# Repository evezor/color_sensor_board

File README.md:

# Color Sensor Board
*please note this board has been deprecated.

Color Sensor board with the VEML6040 chip for color detection with built in led for low light situations.

This also has mousebites on the sensor part of the board so it can be removed and the color sensor can be mounted closer and in a smaller form factor than the larger assembly.

source files can be found here: https://github.com/evezor/v0_color_sensor_board

This board uses the Evezor Stamp STMF405 MCU

source: https://github.com/evezor/Evezor-Stamp-STMF405

Evezor® and all associated marks, logos, and designs are registered trademarks and protected by copyright. Unauthorized use or reproduction of these trademarks and copyrighted materials is strictly prohibited.

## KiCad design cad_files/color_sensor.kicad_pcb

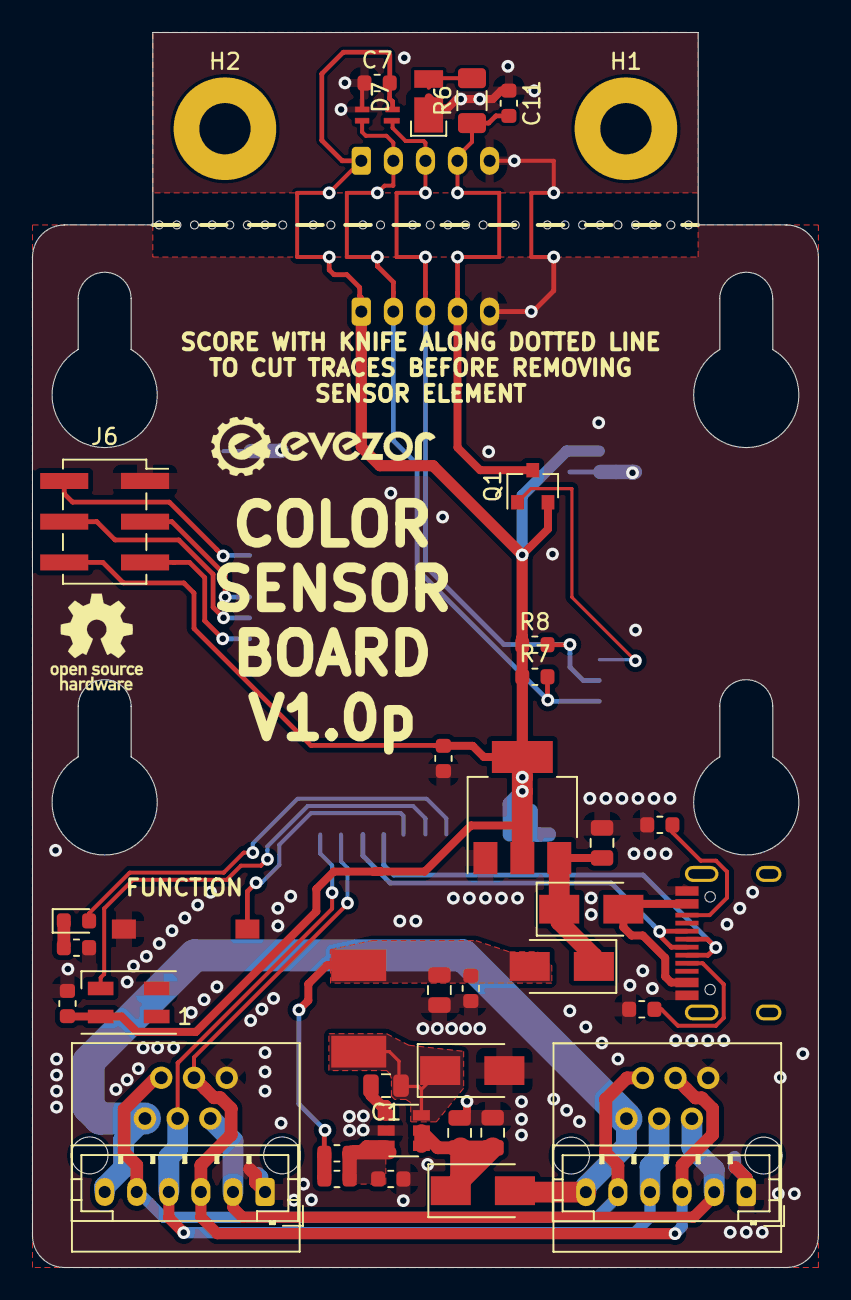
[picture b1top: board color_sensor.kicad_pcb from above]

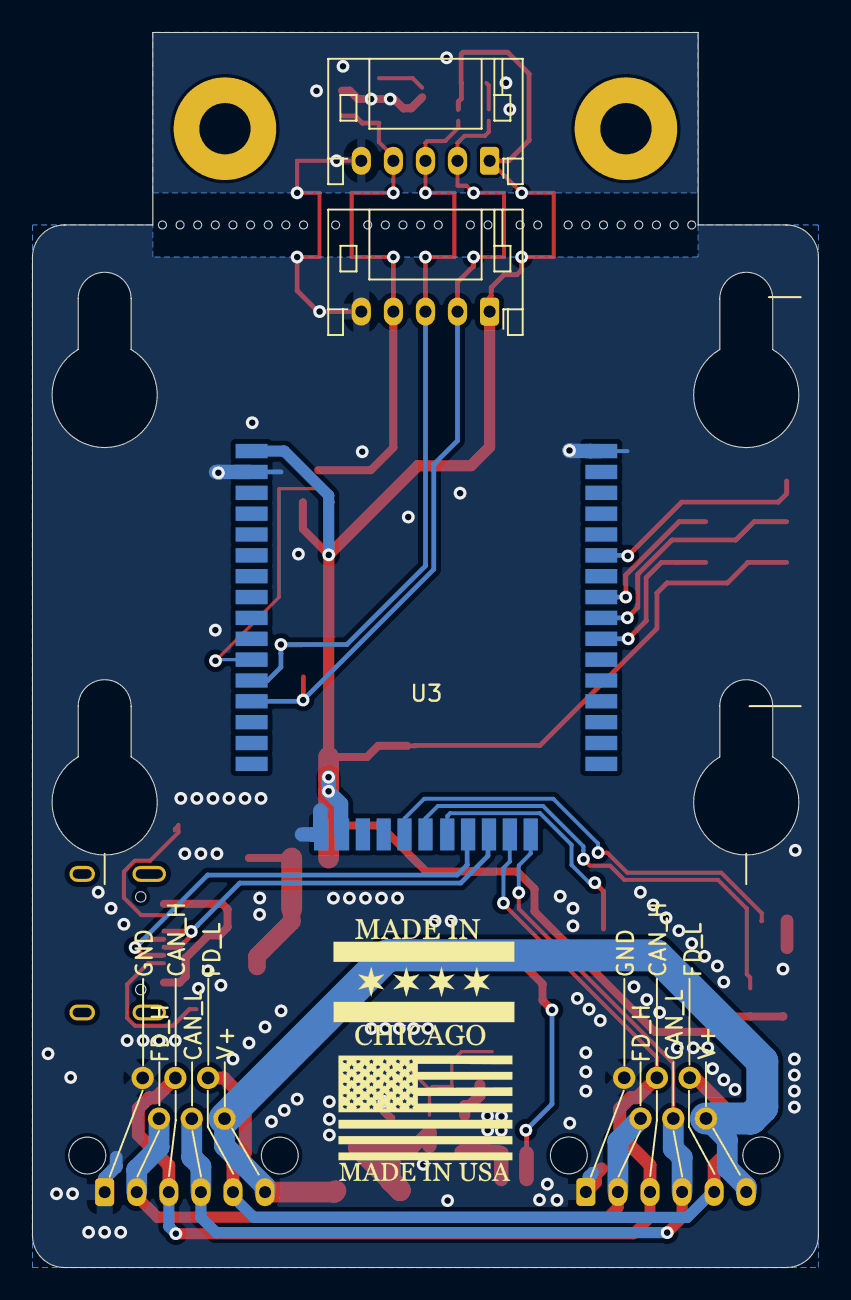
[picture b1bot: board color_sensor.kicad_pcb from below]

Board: 2 copper layers, 49.0 x 77.0 mm, 43 parts (3 on the bottom side), 31 nets.

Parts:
C1, C3: .1uF 100V; C_0805_2012Metric
C2, C5, C7, C9, C10: .1uF; C_0603_1608Metric
C4: 4.7uF; C_0805_2012Metric
C6: 22uF; C_0805_2012Metric
C8: 10uF; C_0805_2012Metric
C11: 10uF; C_0603_1608Metric
D1, D2, D4, D5: SX35_SCHOTTKY; D_SMA
D3: LED; LED_0603_1608Metric
D6: SK6812MINI; LED_SK6812MINI_PLCC4_3.5x3.5mm_P1.75mm
D7: LED; LED_WHITE_CREE_JB2835
H1, H2: MountingHole; MountingHole_3.2mm_M3_Pad
J1: USB_C_Receptacle_USB2.0; USB_C_Receptacle_HRO_TYPE-C-31-M-12
J2, J3: RJ11; RJ11_C189747_Horizontal
J4, J5: PH; JST_PH_B6B-PH-K_1x06_P2.00mm_Vertical
J6: Conn_02x03_Odd_Even; PinSocket_2x03_P2.54mm_Vertical_SMD
J7, J8: Conn_01x05; JST_PH_S5B-PH-K_1x05_P2.00mm_Horizontal
L1: 22uH; INDUCTOR_7.5X6.6_GCDA0630-220MC
Q1: FDC304P; SOT-23
R1: 10k; R_0603_1608Metric
R2: 82k; R_0603_1608Metric
R3, R4: 5.1k; R_0603_1608Metric
R5: 15k; R_0603_1608Metric
R6: 60; R_1206_3216Metric
R7, R8: 4.7k; R_0603_1608Metric
SW1: SW_Push; SWITCH_2x3_SMD_TACTILE_GREEN
U1: SY8401ABC; SOT-23-6
U2: AMS1117-3.3; SOT-223-3_TabPin2
U3: EDGE_STM32F405_CPU_V1; EDGE_STAMP
U4: SENSOR_COLOR_VEML6040

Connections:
+3V3: C7.2, C9.2, C10.1, D6.4, J6.6, J7.1, J8.1, Q1.2, R7.1, R8.1, U2.2, U3.1, U3.18, U4.4
/BACK_LIGHT: Q1.1, U3.11
/BOOT: J6.3, U3.36
/CAN_H: J2.3, J3.3, J4.3, J5.3, U3.26
/CAN_L: J2.4, J3.4, J4.4, J5.4, U3.27
/CC1: J1.A5, R4.1
/CC2: J1.B5, R3.1
/D+: J1.A6, J1.B6, U3.25
/D-: J1.A7, J1.B7, U3.24
/FD_H: J2.2, J3.2, J4.2, J5.2
/FD_L: J2.5, J3.5, J4.5, J5.5
/FUNCTION_BUTTON: SW1.1, U3.23
/HBT_LED: D3.2, U3.21
/LIGHT: C11.2, J7.4, J8.4, Q1.3, R6.1
/NEO_STATUS: D6.3, U3.22
/OLED_SCL: J6.5, U3.34
/OLED_SDA: J6.4, U3.35
/RESET: J6.2, U3.38
/SCL: J7.3, J8.3, R8.2, U3.12, U4.3
/SDA: J7.2, J8.2, R7.2, U3.13, U4.2
/USB_VCC: D4.2, J1.A4, J1.A9, J1.B4, J1.B9
/VREG_OUT: C2.1, C5.1, C6.1, D5.2, L1.2, R2.1
GND: C3.2, C4.2, C5.2, C6.2, C7.1, C8.2, C9.1, C10.2, C11.1, D1.2, D6.2, D7.1, J1.A1, J1.A12, J1.B1, J1.B12, J2.1, J3.1, J4.1, J5.1, J6.1, J7.5, J8.5, R1.1, R3.2, R4.2, R5.1, SW1.2, U1.2, U2.1, U3.2, U3.17, U3.43, U4.1
unnamed: C1.1, D1.1, L1.1, U1.6
unnamed: C1.2, U1.1
unnamed: C2.2, R1.2, R2.2, U1.3
unnamed: C3.1, C4.1, D2.1, U1.4, U1.5
unnamed: C8.1, D4.1, D5.1, U2.3
unnamed: D3.1, R5.2
unnamed: D7.2, R6.2
VBUS: D2.2, J2.6, J3.6, J4.6, J5.6

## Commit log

2023-09-11 Create LICENSE
2023-09-11 add pics
